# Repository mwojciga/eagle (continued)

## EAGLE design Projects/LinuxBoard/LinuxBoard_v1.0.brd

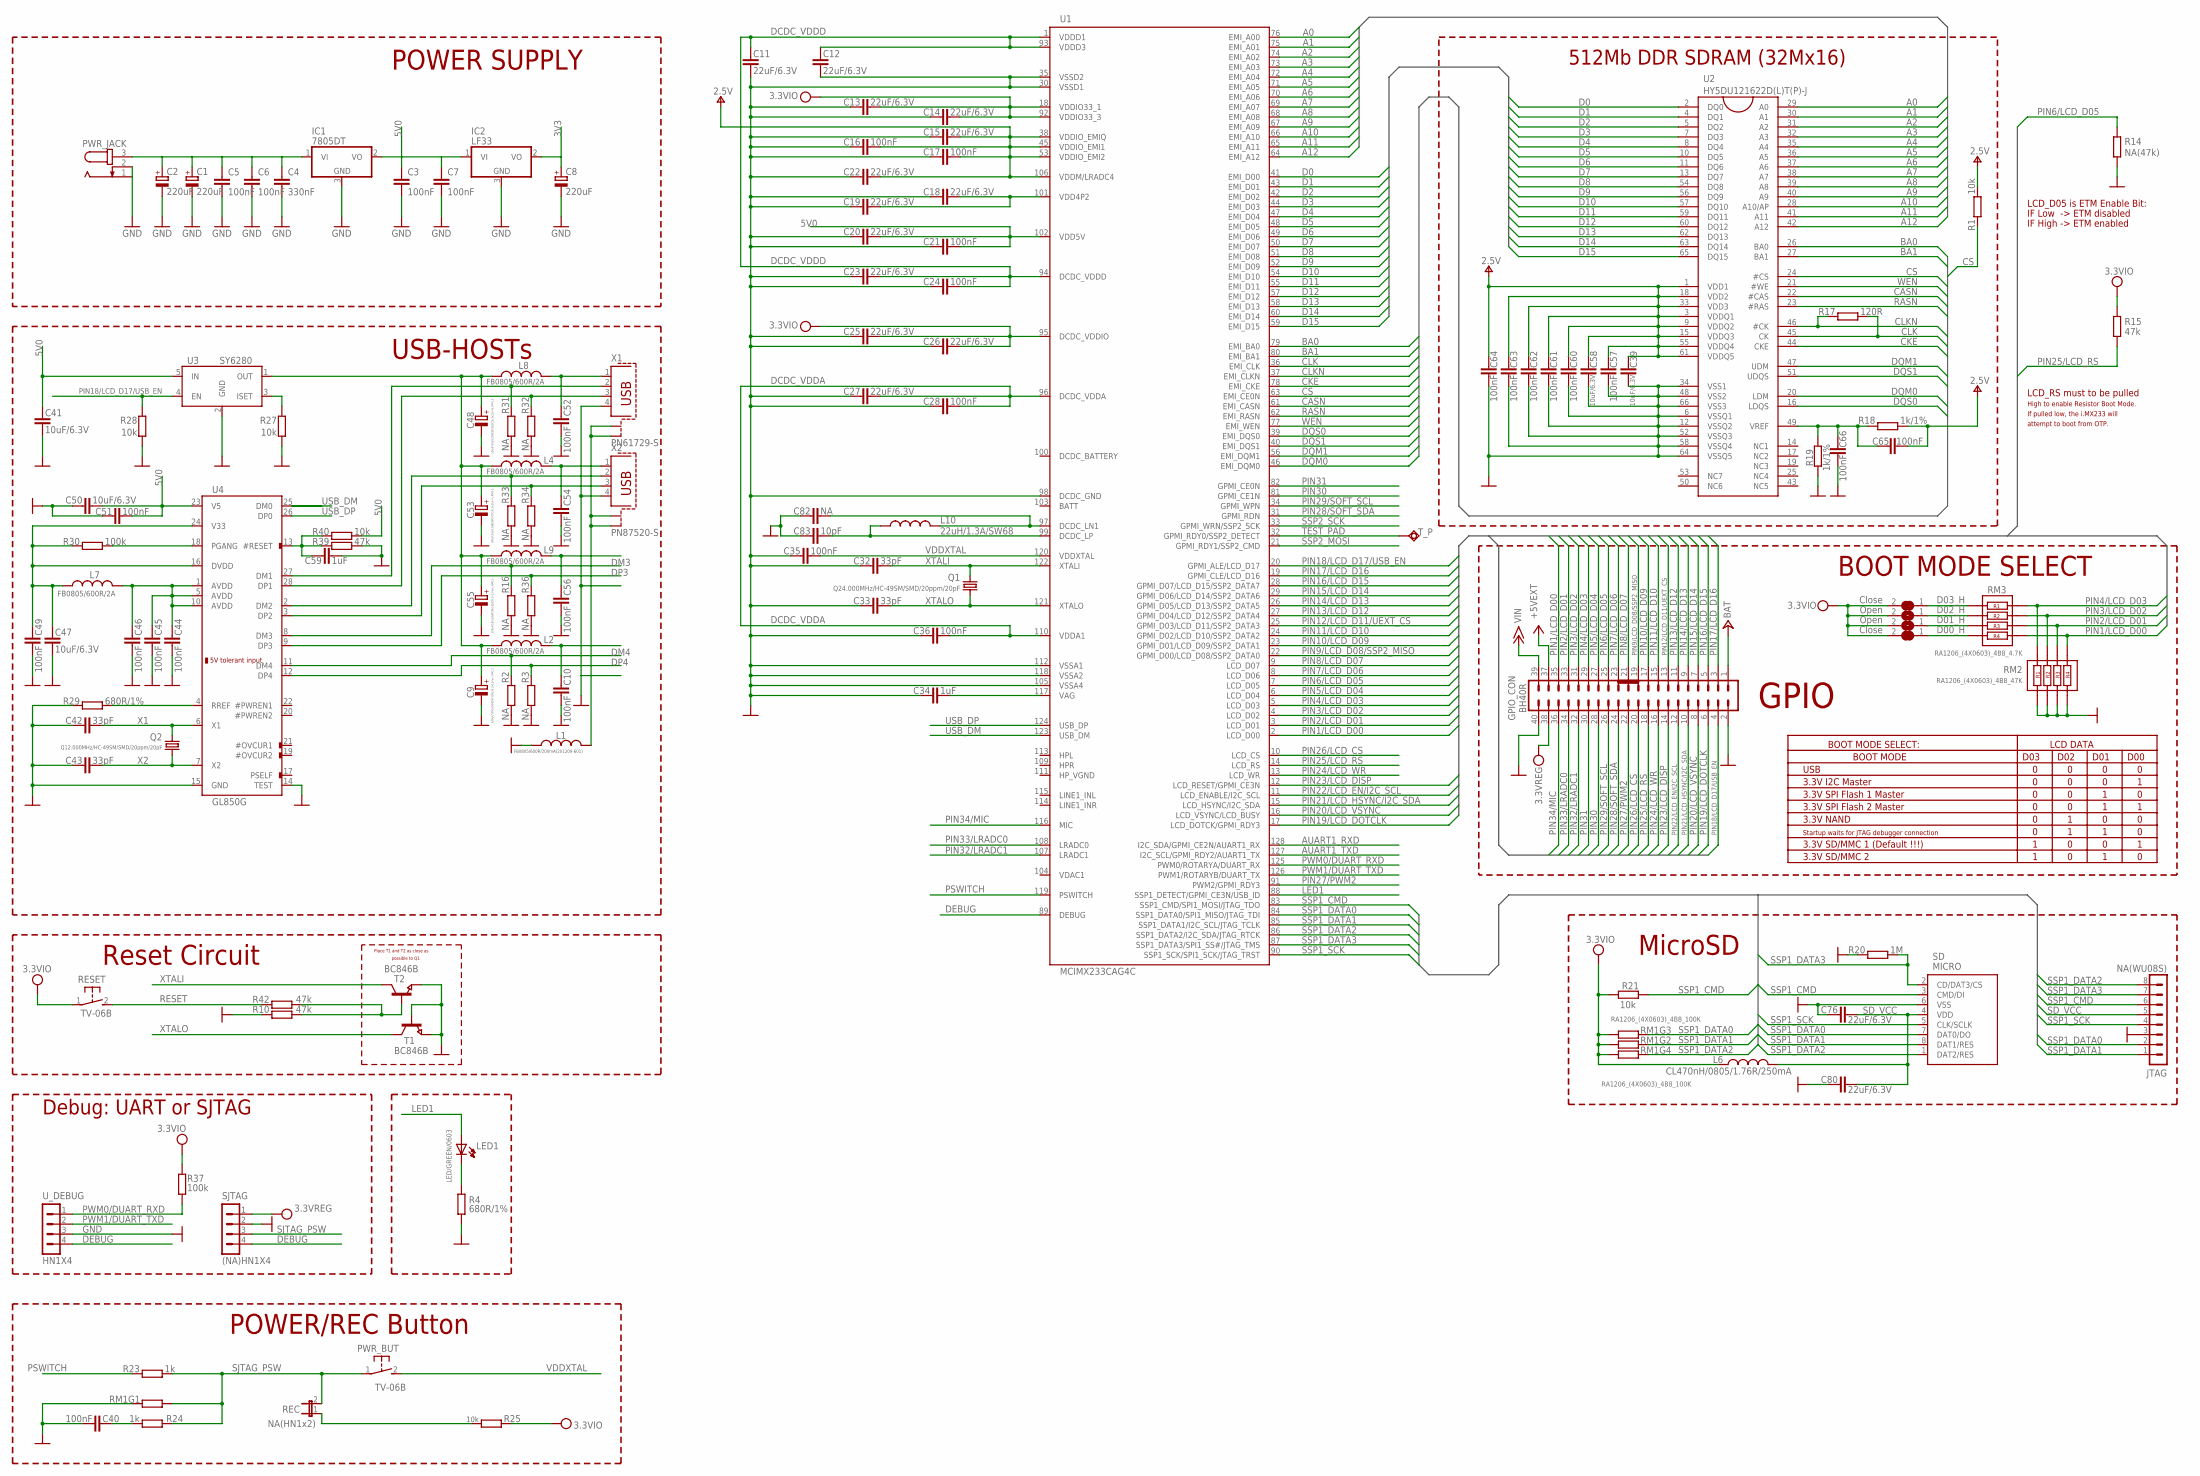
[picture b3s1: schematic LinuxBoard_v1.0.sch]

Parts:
C1, C2, C8: 220uF; E2-5
C3, C5, C6, C7: 100nF; C0805
C4: 330nF; C0805
C9, C48, C53, C55: 100uF/16V/LOWESR/105C/6.3x11mm_RM2.5; E2,5-6,3
C10, C16, C17, C21, C24, C28, C35, C36, C40, C44, C45, C46, C49, C51, C52, C54, C56, C57, C60, C61, C62, C63, C64, C65, C66: 100nF; C0603_DWS
C11, C12, C13, C14, C15, C18, C19, C20, C22, C23, C25, C26, C27, C76, C80: 22uF/6.3V; C0805_5MIL_DWS
C32, C33, C42, C43: 33pF; C0603_DWS
C34, C59: 1uF; C0603_DWS
C39, C41, C47, C50, C58: 10uF/6.3V; C0603_DWS
C82: NA; C0603_DWS
C83: 10pF; C0603_DWS
D00_H, D03_H: Close; SJ_1_SMALLER
D01_H, D02_H: Open; SJ_1_SMALLER
GPIO_CON: BH40R
IC1: 7805DT; TO252
IC2: LF33; TO252
JTAG: NA(WU08S); WU08S
L1: FB0805/600R/200mA(201209-601); L0805_5MIL_DWS
L2, L4, L7, L8, L9: FB0805/600R/2A; L0805_5MIL_DWS
L6: CL470nH/0805/1.76R/250mA; L0805_5MIL_DWS
L10: 22uH/1.3A/SW68; CD53
LED1: LED/GREEN/0603; LED-0603
PWR_BUT: TV-06B; B3F-31XX
PWR_JACK: JACK-PLUG0; SPC4077
Q1: Q24.000MHz/HC-49SM/SMD/20ppm/20pF; HC49/SMD2_THIN
Q2: Q12.000MHz/HC-49SM/SMD/20ppm/20pF; HC49/SMD2_THIN
R1, R21, R27, R28, R40: 10k; R0603_5MIL_DWS
R2, R3, R16, R31, R32, R33, R34, R36: NA; R0603_5MIL_DWS
R4, R29: 680R/1%; R0603_5MIL_DWS
R10, R15, R39, R42: 47k; R0603_5MIL_DWS
R14: NA(47k); R0603_5MIL_DWS
R17: 120R; R0603_5MIL_DWS
R18, R19: 1k/1%; R0603_5MIL_DWS
R20: 1M; R0603_5MIL_DWS
R23, R24: 1k; R0603_5MIL_DWS
R25: 10k; R0603_5MIL_DWS_NA
R30, R37: 100k; R0603_5MIL_DWS
REC: NA(HN1x2); JP1
RESET: TV-06B; B3F-31XX
RM1: RA1206_(4X0603)_4B8_100K; R_MATRIX_4
RM2: RA1206_(4X0603)_4B8_47K; R_MATRIX_4
RM3: RA1206_(4X0603)_4B8_4.7K; R_MATRIX_4
SD: MICRO; TFR-MEM-CON
SJTAG: (NA)HN1X4; HN1X4
T1, T2: BC846B; SOT23
T_P: TESTPAD50/40; SMD50/40
U1: MCIMX233CAG4C; TQFP128LD
U2: HY5DU121622D(L)T(P)-J; 66TSOP-II
U3: SY6280; SOT23-5
U4: GL850G; SSOP28
U_DEBUG: HN1X4
X1: PN61729-S
X2: PN87520-S

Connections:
3V3: C8.+, IC2.2 (VO)
5V0: C3.1, C7.1, C20.2, C21.2, C41.1, C50.1, C51.1, IC1.2 (VO), IC2.1 (VI), R40.2, U1.102 (VDD5V), U3.5 (IN), U4.23 (V5)
+5V: GPIO_CON.37
+15V: GPIO_CON.39
+24V: GPIO_CON.1
A0: U1.76 (EMI_A00), U2.29 (A0)
A1: U1.75 (EMI_A01), U2.30 (A1)
A2: U1.74 (EMI_A02), U2.31 (A2)
A3: U1.73 (EMI_A03), U2.32 (A3)
A4: U1.72 (EMI_A04), U2.35 (A4)
A5: U1.71 (EMI_A05), U2.36 (A5)
A6: U1.70 (EMI_A06), U2.37 (A6)
A7: U1.69 (EMI_A07), U2.38 (A7)
A8: U1.68 (EMI_A08), U2.39 (A8)
A9: U1.67 (EMI_A09), U2.40 (A9)
A10: U1.66 (EMI_A10), U2.28 (A10/AP)
A11: U1.65 (EMI_A11), U2.41 (A11)
A12: U1.64 (EMI_A12), U2.42 (A12)
AUART1_RXD: U1.128 (I2C_SDA/GPMI_CE2N/AUART1_RX)
AUART1_TXD: U1.127 (I2C_SCL/GPMI_RDY2/AUART1_TX)
BA0: U1.79 (EMI_BA0), U2.26 (BA0)
BA1: U1.80 (EMI_BA1), U2.27 (BA1)
CASN: U1.61 (EMI_CASN), U2.22 (#CAS)
CKE: U1.78 (EMI_CKE), U2.44 (CKE)
CLK: R17.2, U1.36 (EMI_CLK), U2.45 (CK)
CLKN: R17.1, U1.37 (EMI_CLKN), U2.46 (#CK)
CS: R1.1, U1.63 (EMI_CE0N), U2.24 (#CS)
D0: U1.41 (EMI_D00), U2.2 (DQ0)
D1: U1.43 (EMI_D01), U2.4 (DQ1)
D2: U1.42 (EMI_D02), U2.5 (DQ2)
D3: U1.44 (EMI_D03), U2.7 (DQ3)
D4: U1.47 (EMI_D04), U2.8 (DQ4)
D5: U1.48 (EMI_D05), U2.10 (DQ5)
D6: U1.49 (EMI_D06), U2.11 (DQ6)
D7: U1.50 (EMI_D07), U2.13 (DQ7)
D8: U1.51 (EMI_D08), U2.54 (DQ8)
D9: U1.52 (EMI_D09), U2.56 (DQ9)
D10: U1.54 (EMI_D10), U2.57 (DQ10)
D11: U1.55 (EMI_D11), U2.59 (DQ11)
D12: U1.57 (EMI_D12), U2.60 (DQ12)
D13: U1.58 (EMI_D13), U2.62 (DQ13)
D14: U1.60 (EMI_D14), U2.63 (DQ14)
D15: U1.59 (EMI_D15), U2.65 (DQ15)
DCDC_BATTERY: U1.100 (DCDC_BATTERY)
DCDC_VDDA: C27.2, C28.2, C36.2, U1.96 (DCDC_VDDA), U1.110 (VDDA1)
DCDC_VDDD: C11.2, C12.2, C23.2, C24.2, U1.1 (VDDD1), U1.93 (VDDD3), U1.94 (DCDC_VDDD)
DEBUG: SJTAG.4, U1.89 (DEBUG), U_DEBUG.4
DM3: R16.2, U4.8 (DM3)
DM4: R2.2, U4.11 (DM4)
DP3: R36.2, U4.9 (DP3)
DP4: R3.2, U4.12 (DP4)
DQM0: U1.46 (EMI_DQM0), U2.20 (LDM)
DQM1: U1.56 (EMI_DQM1), U2.47 (UDM)
DQS0: U1.39 (EMI_DQS0), U2.16 (LDQS)
DQS1: U1.40 (EMI_DQS1), U2.51 (UDQS)
GND: C1.-, C2.-, C3.2, C4.2, C5.2, C6.2, C7.2, C8.-, C9.-, C10.2, C11.1, C12.1, C13.1, C14.1, C15.1, C16.1, C17.1, C18.1, C19.1, C20.1, C21.1, C22.1, C23.1, C24.1, C25.1, C26.1, C27.1, C28.1, C32.1, C33.1, C34.1, C35.1, C36.1, C39.1, C40.2, C41.2, C42.1, C43.1, C44.2, C45.2, C46.2, C47.2, C48.-, C49.2, C50.2, C51.2, C52.2, C53.-, C54.2, C55.-, C56.2, C57.1, C58.1, C59.1, C60.1, C61.1, C62.1, C63.1, C64.1, C66.1, C76.1, C80.1, C82.1, C83.1, GPIO_CON.2, GPIO_CON.40, IC1.3 (GND), IC2.3 (GND), JTAG.3, L1.1, PWR_JACK.1, PWR_JACK.2, R2.1, R3.1, R4.1, R10.2, R14.1, R16.1, R19.1, R20.2, R27.1, R28.1, R29.1, R31.1, R32.1, R33.1, R34.1, R36.1, R39.2, RM1.1.1 (1), RM2.1.1, RM2.2.1, RM2.3.1, RM2.4.1, SD.6 (VSS), SJTAG.2, T1.1 (B), T1.2 (E), T2.2 (E), U1.30 (VSSD1), U1.35 (VSSD2), U1.98 (DCDC_GND), U1.105 (VSSA4), U1.112 (VSSA1), U1.118 (VSSA2), U2.6 (VSSQ1), U2.12 (VSSQ2), U2.34 (VSS1), U2.48 (VSS2), U2.52 (VSSQ3), U2.58 (VSSQ4), U2.64 (VSSQ5), U2.66 (VSS3), U3.2 (GND), U4.14 (TEST), U4.15 (GND), U_DEBUG.3, X1.4, X2.4
HP_VGND: U1.111 (HP_VGND)
LED1: LED1.A, U1.88 (SSP1_DETECT/GPMI_CE3N/USB_ID)
unnamed: R27.2, U3.3 (ISET)
unnamed: R29.2, U4.4 (RREF)
unnamed: R30.2, U4.18 (PGANG)
unnamed: C59.2, R39.1, R40.1, U4.13 (#RESET)
unnamed: C10.1, L2.2
unnamed: C9.+, C48.+, C53.+, C55.+, L2.1, L4.1, L8.1, L9.1, U3.1 (OUT)
unnamed: R31.2, U4.27 (DM1), X1.2
unnamed: C44.1, C45.1, C46.1, L7.2, U4.1 (AVDD), U4.5 (AVDD), U4.10 (AVDD)
unnamed: C47.1, C49.1, L7.1, R30.1, U4.16 (DVDD), U4.24 (V33)
unnamed: R32.2, U4.28 (DP1), X1.3
unnamed: R33.2, U4.2 (DM2), X2.2
unnamed: R34.2, U4.3 (DP2), X2.3
unnamed: L1.2, X1.S1, X1.S2, X2.S1, X2.S2
unnamed: C65.2, C66.2, R18.1, R19.2, U2.49 (VREF)
unnamed: C82.2, L10.2, U1.97 (DCDC_LN1)
unnamed: C83.2, L10.1, U1.99 (DCDC_LP)
unnamed: C52.1, L8.2, X1.1
unnamed: C54.1, L4.2, X2.1
unnamed: C34.2, U1.117 (VAG)
unnamed: C56.1, L9.2
unnamed: C40.1, R24.1
unnamed: R25.1, REC.1
unnamed: LED1.C, R4.2
unnamed: R10.1, R42.1, T2.1 (B)
unnamed: D03_H.1, RM3.1.2
unnamed: D02_H.1, RM3.2.2
unnamed: D01_H.1, RM3.3.2
unnamed: D00_H.1, RM3.4.2
PIN1/LCD_D00: GPIO_CON.35, RM2.4.2, RM3.4.1, U1.2 (LCD_D00)
PIN2/LCD_D01: GPIO_CON.33, RM2.3.2, RM3.3.1, U1.3 (LCD_D01)
PIN3/LCD_D02: GPIO_CON.31, RM2.2.2, RM3.2.1, U1.4 (LCD_D02)
PIN4/LCD_D03: GPIO_CON.29, RM2.1.2, RM3.1.1, U1.5 (LCD_D03)
PIN5/LCD_D04: GPIO_CON.27, U1.6 (LCD_D04)
PIN6/LCD_D05: GPIO_CON.25, R14.2, U1.7 (LCD_D05)
PIN7/LCD_D06: GPIO_CON.23, U1.8 (LCD_D06)
PIN8/LCD_D07: GPIO_CON.21, U1.9 (LCD_D07)
PIN9/LCD_D08/SSP2_MISO: GPIO_CON.19, U1.22 (GPMI_D00/LCD_D08/SSP2_DATA0)
PIN10/LCD_D09: GPIO_CON.17, U1.23 (GPMI_D01/LCD_D09/SSP2_DATA1)
PIN11/LCD_D10: GPIO_CON.15, U1.24 (GPMI_D02/LCD_D10/SSP2_DATA2)
PIN12/LCD_D11/UEXT_CS: GPIO_CON.13, U1.25 (GPMI_D03/LCD_D11/SSP2_DATA3)
PIN13/LCD_D12: GPIO_CON.11, U1.27 (GPMI_D04/LCD_D12/SSP2_DATA4)
PIN14/LCD_D13: GPIO_CON.9, U1.26 (GPMI_D05/LCD_D13/SSP2_DATA5)
PIN15/LCD_D14: GPIO_CON.7, U1.29 (GPMI_D06/LCD_D14/SSP2_DATA6)
PIN16/LCD_D15: GPIO_CON.5, U1.28 (GPMI_D07/LCD_D15/SSP2_DATA7)
PIN17/LCD_D16: GPIO_CON.3, U1.19 (GPMI_CLE/LCD_D16)
PIN18/LCD_D17/USB_EN: GPIO_CON.4, R28.2, U1.20 (GPMI_ALE/LCD_D17), U3.4 (EN)
PIN19/LCD_DOTCLK: GPIO_CON.6, U1.17 (LCD_DOTCK/GPMI_RDY3)
PIN20/LCD_VSYNC: GPIO_CON.8, U1.16 (LCD_VSYNC/LCD_BUSY)
PIN21/LCD_HSYNC/I2C_SDA: GPIO_CON.10, U1.15 (LCD_HSYNC/I2C_SDA)
PIN22/LCD_EN/I2C_SCL: GPIO_CON.12, U1.11 (LCD_ENABLE/I2C_SCL)
PIN23/LCD_DISP: GPIO_CON.14, U1.12 (LCD_RESET/GPMI_CE3N)
PIN24/LCD_WR: GPIO_CON.16, U1.13 (LCD_WR)
PIN25/LCD_RS: GPIO_CON.18, R15.2, U1.14 (LCD_RS)
PIN26/LCD_CS: GPIO_CON.20, U1.10 (LCD_CS)
PIN27/PWM2: GPIO_CON.22, U1.91 (PWM2/GPMI_RDY3)
PIN28/SOFT_SDA: GPIO_CON.24, U1.31 (GPMI_RDN)
PIN29/SOFT_SCL: GPIO_CON.26, U1.34 (GPMI_WPN)
PIN30: GPIO_CON.28, U1.81 (GPMI_CE1N)
PIN31: GPIO_CON.30, U1.82 (GPMI_CE0N)
PIN32/LRADC1: GPIO_CON.32, U1.107 (LRADC1)
PIN33/LRADC0: GPIO_CON.34, U1.108 (LRADC0)
PIN34/MIC: GPIO_CON.36, U1.116 (MIC)
PSWITCH: R23.1, U1.119 (PSWITCH)
PWM0/DUART_RXD: R37.1, U1.125 (PWM0/ROTARYA/DUART_RX), U_DEBUG.1
PWM1/DUART_TXD: U1.126 (PWM1/ROTARYB/DUART_TX), U_DEBUG.2
RASN: U1.62 (EMI_RASN), U2.23 (#RAS)
RESET: R42.2, RESET.2 (S)
SD_VCC: C76.2, C80.2, JTAG.5, L6.2, SD.4 (VDD)
SJTAG_PSW: PWR_BUT.1, R23.2, R24.2, REC.2, RM1.1.2 (2), SJTAG.3
SSP1_CMD: JTAG.6, R21.1, SD.3 (CMD/DI), U1.83 (SSP1_CMD/SPI1_MOSI/JTAG_TDO)
SSP1_DATA0: JTAG.2, RM1.3.1 (1), SD.7 (DAT0/DO), U1.84 (SSP1_DATA0/SPI1_MISO/JTAG_TDI)
SSP1_DATA1: JTAG.1, RM1.2.1 (1), SD.8 (DAT1/RES), U1.85 (SSP1_DATA1/I2C_SCL/JTAG_TCLK)
SSP1_DATA2: JTAG.8, RM1.4.1 (1), SD.1 (DAT2/RES), U1.86 (SSP1_DATA2/I2C_SDA/JTAG_RTCK)
SSP1_DATA3: JTAG.7, R20.1, SD.2 (CD/DAT3/CS), U1.87 (SSP1_DATA3/SPI1_SS#/JTAG_TMS)
SSP1_SCK: JTAG.4, SD.5 (CLK/SCLK), U1.90 (SSP1_SCK/SPI1_SCK/JTAG_TRST)
SSP2_MOSI: U1.21 (GPMI_RDY1/SSP2_CMD)
SSP2_SCK: U1.33 (GPMI_WRN/SSP2_SCK)
TEST_PAD: T_P.P$1, U1.32 (GPMI_RDY0/SSP2_DETECT)
USB_DM: U1.123 (USB_DM), U4.25 (DM0)
USB_DP: U1.124 (USB_DP), U4.26 (DP0)
V+: C15.2, C16.2, C17.2, C22.2, C39.2, C57.2, C58.2, C60.2, C61.2, C62.2, C63.2, C64.2, C65.1, R1.2, R18.2, U1.38 (VDDIO_EMIQ), U1.45 (VDDIO_EMI1), U1.53 (VDDIO_EMI2), U1.106 (VDDM/LRADC4), U2.1 (VDD1), U2.3 (VDDQ1), U2.9 (VDDQ2), U2.15 (VDDQ3), U2.18 (VDD2), U2.33 (VDD3), U2.55 (VDDQ4), U2.61 (VDDQ5)
VCC: GPIO_CON.38, SJTAG.1
VDD4P2: C18.2, C19.2, U1.101 (VDD4P2)
VDDXTAL: C35.2, PWR_BUT.2 (S), U1.120 (VDDXTAL)
VIN_JACK: C1.+, C2.+, C4.1, C5.1, C6.1, IC1.1 (VI), PWR_JACK.3
VPP: C13.2, C14.2, C25.2, C26.2, D00_H.2, D01_H.2, D02_H.2, D03_H.2, L6.1, R15.1, R21.2, R25.2, R37.2, RESET.1, RM1.2.2 (2), RM1.3.2 (2), RM1.4.2 (2), U1.18 (VDDIO33_1), U1.92 (VDDIO33_3), U1.95 (DCDC_VDDIO)
WEN: U1.77 (EMI_WEN), U2.21 (#WE)
X1: C42.2, Q2.2, U4.6 (X1)
X2: C43.2, Q2.1, U4.7 (X2)
XTALI: C32.2, Q1.2, T2.3 (C), U1.122 (XTALI)
XTALO: C33.2, Q1.1, T1.3 (C), U1.121 (XTALO)

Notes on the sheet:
USB-HOSTs
POWER SUPPLY
Place T1 and T2 as close as
possible to Q1
Reset Circuit
512Mb DDR SDRAM (32Mx16)
MicroSD
POWER/REC Button
BOOT MODE SELECT
BOOT MODE SELECT:
LCD DATA
BOOT MODE
D03
D02
D01
D00
USB
3.3V I2C Master
3.3V SPI Flash 1 Master
3.3V SPI Flash 2 Master
3.3V NAND
Startup waits for JTAG debugger connection
3.3V SD/MMC 1 (Default !!!)
3.3V SD/MMC 2
LCD_RS must to be pulled
High to enable Resistor Boot Mode.
If pulled low, the i.MX233 will
attempt to boot from OTP.
LCD_D05 is ETM Enable Bit:
IF Low -> ETM disabled
IF High -> ETM enabled
GPIO
Debug: UART or SJTAG

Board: 2 copper layers, 132 parts (0 on the bottom side), 140 nets, no tracks yet.

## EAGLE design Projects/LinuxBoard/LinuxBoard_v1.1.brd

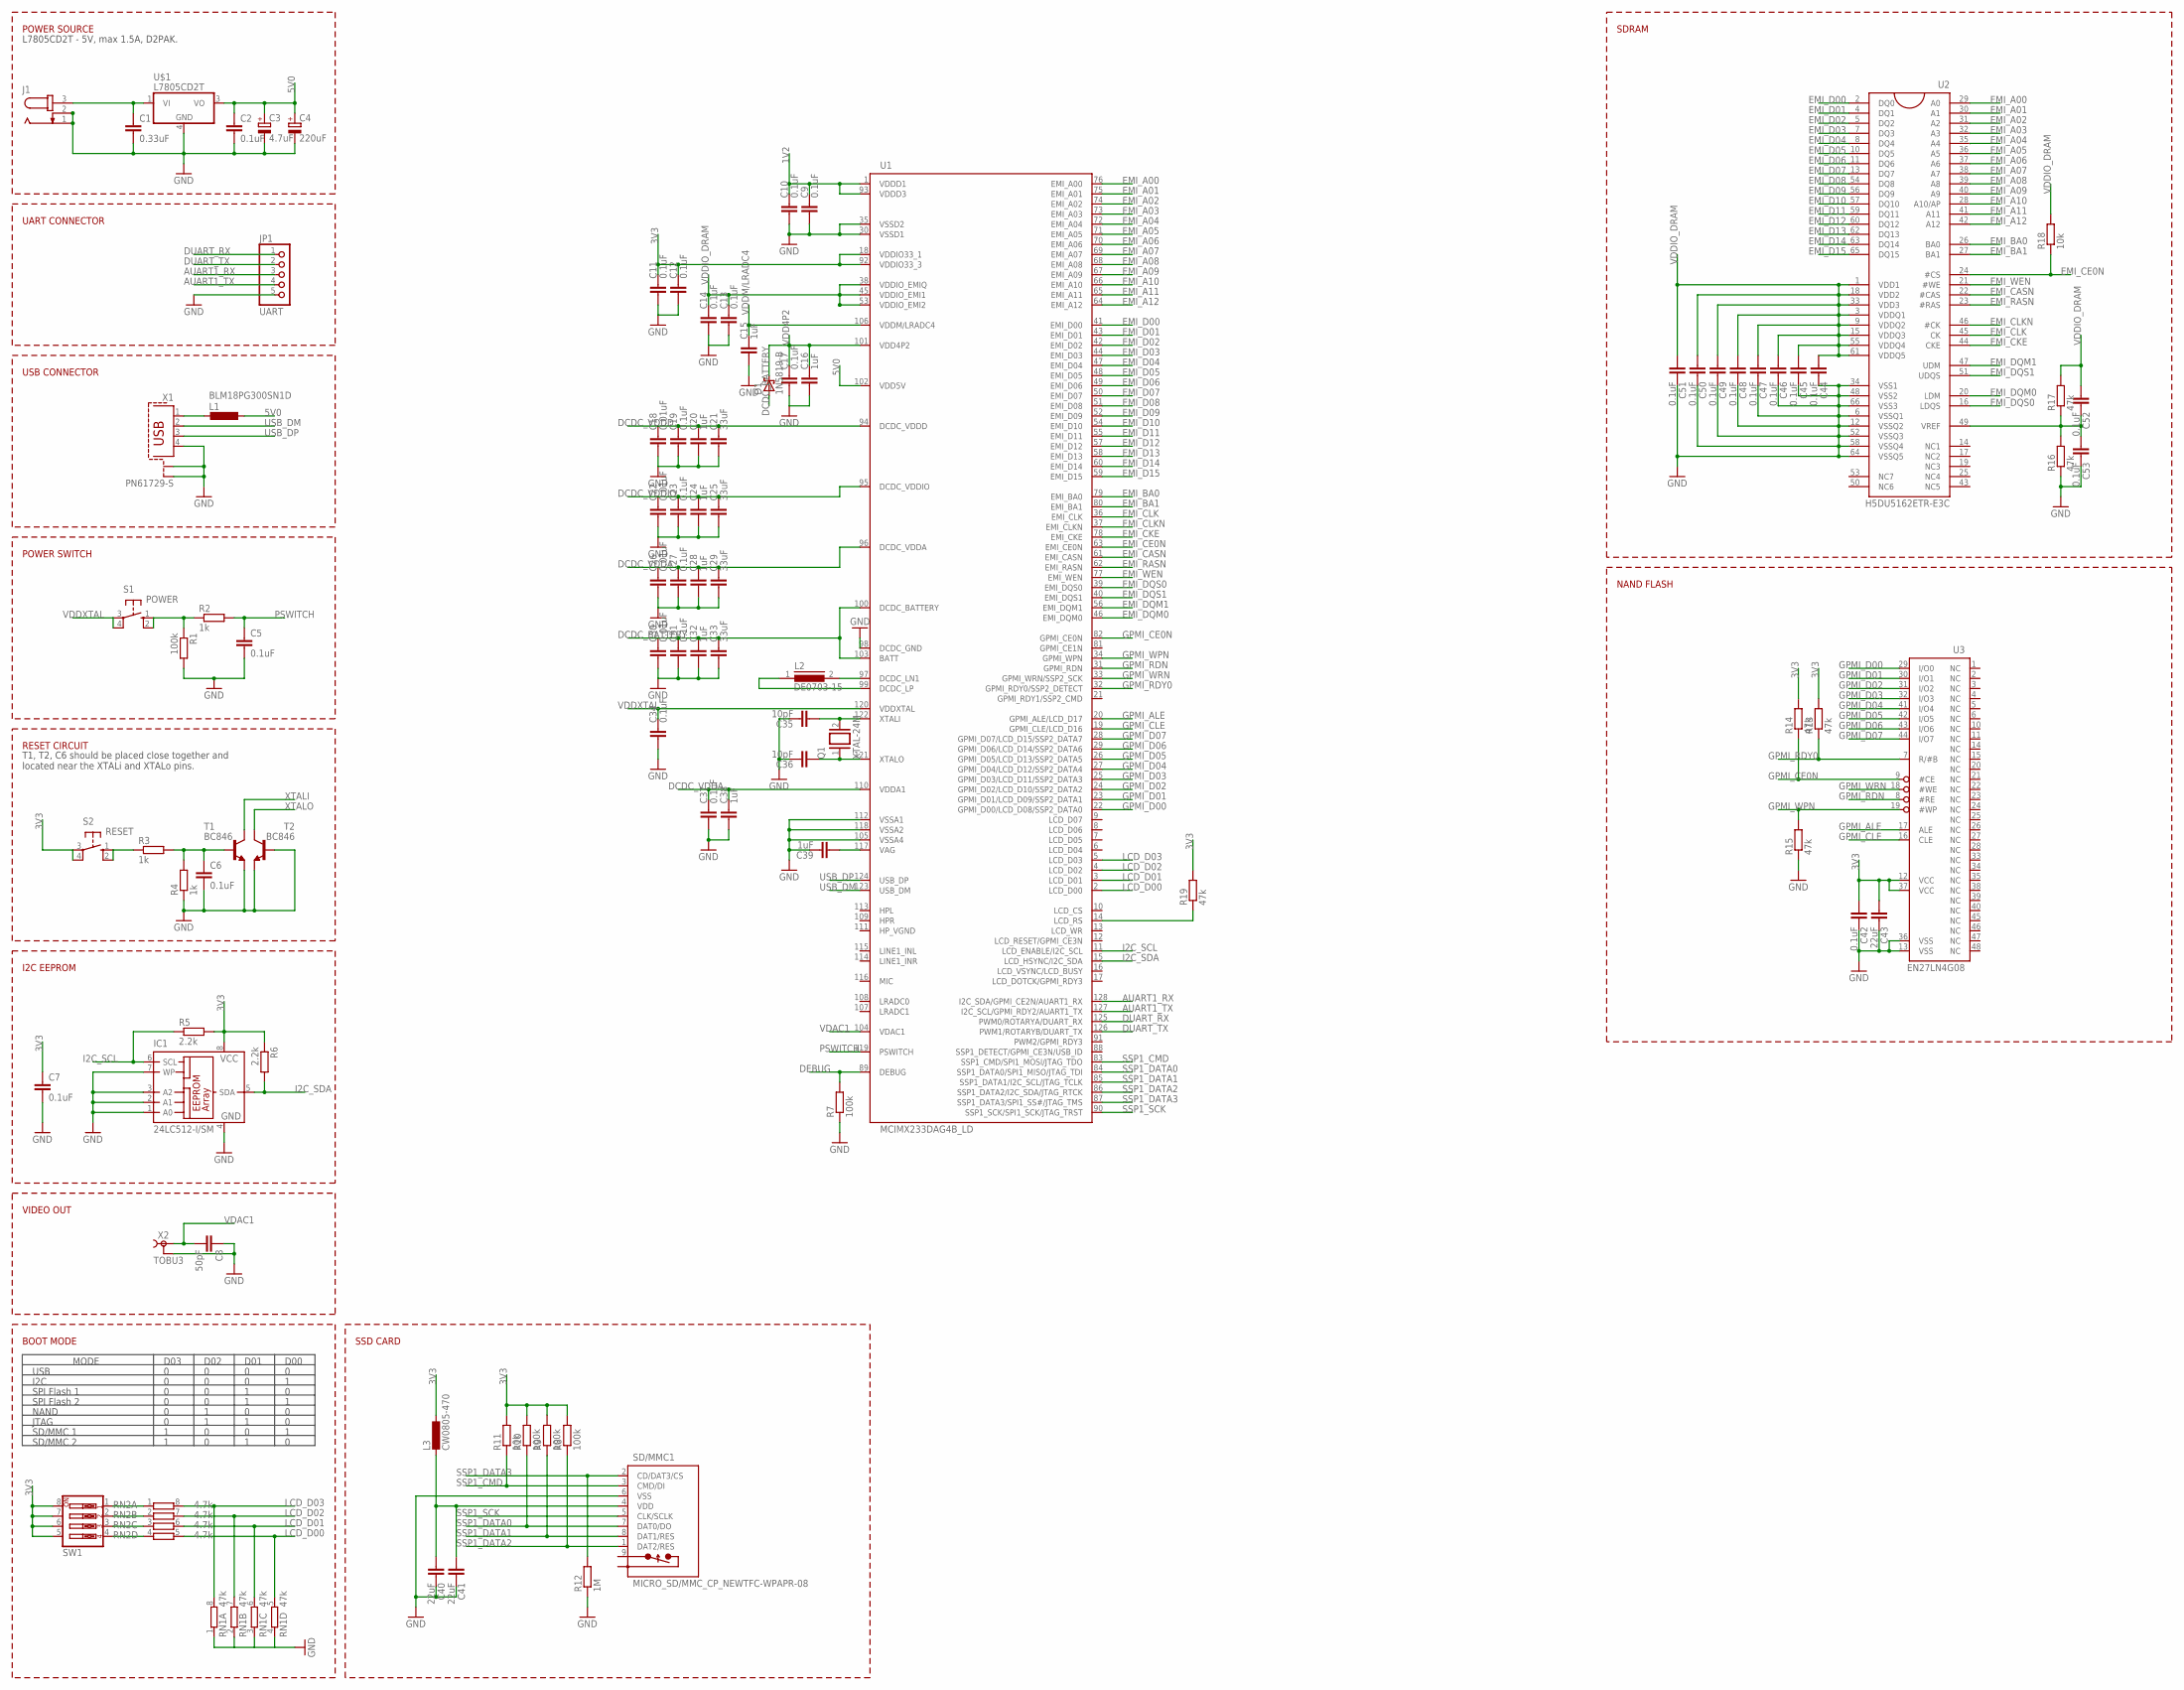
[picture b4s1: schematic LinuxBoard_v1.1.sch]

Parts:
C1: 0.33uF; C0805
C2, C5, C6, C7, C9, C10, C11, C12, C13, C14, C17, C19, C23, C27, C31, C34, C37, C42, C44, C45, C46, C47, C48, C49, C50, C51, C52, C53: 0.1uF; C0805
C3: 4.7uF; E2-5
C4: 220uF; E2-5
C8: 50pF; C0805
C15, C16, C20, C24, C28, C32, C38, C39: 1uF; C0805
C18, C22, C26, C30: 0.01uF; C0805
C21, C25, C29, C33: 33uF; C0805
C35, C36: 10pF; C0805
C40, C41, C43: 22uF; C0805
D1: 1N5819-B; DO41-7.6
IC1: 24LC512-I/SM; SO-08
J1: JACK-PLUG0; SPC4077
JP1: UART; 1X05
L1: BLM18PG300SN1D; L0201
L2: DE0703-15; DR73
L3: CW0805-470; L2012C
Q1: XTAL-24M; QS
R1, R7, R8, R9, R10: 100k; R0805
R2, R3, R4: 1k; R0805
R5, R6: 2.2k; R0805
R11, R18: 10k; R0805
R12: 1M; R0805
R13, R14, R15, R16, R17, R19: 47k; R0805
RN1: 47k; YC124
RN2: 4.7k; YC124
S1: POWER; B3F-10XX
S2: RESET; B3F-10XX
SD/MMC1: MICRO_SD/MMC_CP_NEWTFC-WPAPR-08; TFC-WPAPR-08
SW1: SW_DIP-4; EDG-04
T1, T2: BC846; SOT23
U1: MCIMX233DAG4B_LD; TQFP128LD
U2: H5DU5162ETR-E3C; 66TSOP-II
U3: EN27LN4G08; TSOP48
U$1: L7805CD2T; D2PAK-3
X1: PN61729-S
X2: TOBU3

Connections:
1V2: C9.1, C10.1, U1.1 (VDDD1), U1.93 (VDDD3)
3V3: C7.1, C11.1, C12.1, C42.2, C43.2, IC1.8 (VCC), L3.1, R5.2, R6.1, R8.2, R9.2, R10.2, R11.2, R13.2, R14.2, R19.2, S2.3, S2.4 (P1), SW1.5, SW1.6, SW1.7, SW1.8, U1.18 (VDDIO33_1), U1.92 (VDDIO33_3), U3.12 (VCC), U3.37 (VCC)
5V0: C2.1, C3.+, C4.+, L1.1, U1.102 (VDD5V), U$1.3 (VO)
AUART1_RX: JP1.3, U1.128 (I2C_SDA/GPMI_CE2N/AUART1_RX)
AUART1_TX: JP1.4, U1.127 (I2C_SCL/GPMI_RDY2/AUART1_TX)
DCDC_BATTERY: C30.1, C31.1, C32.1, C33.1, D1.A, U1.100 (DCDC_BATTERY), U1.103 (BATT)
DCDC_VDDA: C26.1, C27.1, C28.1, C29.1, C37.1, C38.1, U1.96 (DCDC_VDDA), U1.110 (VDDA1)
DCDC_VDDD: C18.1, C19.1, C20.1, C21.1, U1.94 (DCDC_VDDD)
DCDC_VDDIO: C22.1, C23.1, C24.1, C25.1, U1.95 (DCDC_VDDIO)
DEBUG: R7.2, U1.89 (DEBUG)
DUART_RX: JP1.1, U1.125 (PWM0/ROTARYA/DUART_RX)
DUART_TX: JP1.2, U1.126 (PWM1/ROTARYB/DUART_TX)
EMI_A00: U1.76 (EMI_A00), U2.29 (A0)
EMI_A01: U1.75 (EMI_A01), U2.30 (A1)
EMI_A02: U1.74 (EMI_A02), U2.31 (A2)
EMI_A03: U1.73 (EMI_A03), U2.32 (A3)
EMI_A04: U1.72 (EMI_A04), U2.35 (A4)
EMI_A05: U1.71 (EMI_A05), U2.36 (A5)
EMI_A06: U1.70 (EMI_A06), U2.37 (A6)
EMI_A07: U1.69 (EMI_A07), U2.38 (A7)
EMI_A08: U1.68 (EMI_A08), U2.39 (A8)
EMI_A09: U1.67 (EMI_A09), U2.40 (A9)
EMI_A10: U1.66 (EMI_A10), U2.28 (A10/AP)
EMI_A11: U1.65 (EMI_A11), U2.41 (A11)
EMI_A12: U1.64 (EMI_A12), U2.42 (A12)
EMI_BA0: U1.79 (EMI_BA0), U2.26 (BA0)
EMI_BA1: U1.80 (EMI_BA1), U2.27 (BA1)
EMI_CASN: U1.61 (EMI_CASN), U2.22 (#CAS)
EMI_CE0N: R18.1, U1.63 (EMI_CE0N), U2.24 (#CS)
EMI_CKE: U1.78 (EMI_CKE), U2.44 (CKE)
EMI_CLK: U1.36 (EMI_CLK), U2.45 (CK)
EMI_CLKN: U1.37 (EMI_CLKN), U2.46 (#CK)
EMI_D00: U1.41 (EMI_D00), U2.2 (DQ0)
EMI_D01: U1.43 (EMI_D01), U2.4 (DQ1)
EMI_D02: U1.42 (EMI_D02), U2.5 (DQ2)
EMI_D03: U1.44 (EMI_D03), U2.7 (DQ3)
EMI_D04: U1.47 (EMI_D04), U2.8 (DQ4)
EMI_D05: U1.48 (EMI_D05), U2.10 (DQ5)
EMI_D06: U1.49 (EMI_D06), U2.11 (DQ6)
EMI_D07: U1.50 (EMI_D07), U2.13 (DQ7)
EMI_D08: U1.51 (EMI_D08), U2.54 (DQ8)
EMI_D09: U1.52 (EMI_D09), U2.56 (DQ9)
EMI_D10: U1.54 (EMI_D10), U2.57 (DQ10)
EMI_D11: U1.55 (EMI_D11), U2.59 (DQ11)
EMI_D12: U1.57 (EMI_D12), U2.60 (DQ12)
EMI_D13: U1.58 (EMI_D13), U2.62 (DQ13)
EMI_D14: U1.60 (EMI_D14), U2.63 (DQ14)
EMI_D15: U1.59 (EMI_D15), U2.65 (DQ15)
EMI_DQM0: U1.46 (EMI_DQM0), U2.20 (LDM)
EMI_DQM1: U1.56 (EMI_DQM1), U2.47 (UDM)
EMI_DQS0: U1.39 (EMI_DQS0), U2.16 (LDQS)
EMI_DQS1: U1.40 (EMI_DQS1), U2.51 (UDQS)
EMI_RASN: U1.62 (EMI_RASN), U2.23 (#RAS)
EMI_WEN: U1.77 (EMI_WEN), U2.21 (#WE)
GND: C1.2, C2.2, C3.-, C4.-, C5.2, C6.2, C7.2, C8.1, C9.2, C10.2, C11.2, C12.2, C13.2, C14.2, C15.2, C16.2, C17.2, C18.2, C19.2, C20.2, C21.2, C22.2, C23.2, C24.2, C25.2, C26.2, C27.2, C28.2, C29.2, C30.2, C31.2, C32.2, C33.2, C34.2, C35.1, C36.1, C37.2, C38.2, C39.1, C40.1, C41.1, C42.1, C43.1, C44.1, C45.1, C46.1, C47.1, C48.1, C49.1, C50.1, C51.1, C53.1, IC1.1 (A0), IC1.2 (A1), IC1.3 (A2), IC1.4 (GND), IC1.7 (WP), J1.1, J1.2, JP1.5, R1.2, R4.1, R7.1, R12.1, R15.1, R16.1, RN1.1, RN1.2 (1), RN1.3 (1), RN1.4 (1), SD/MMC1.6 (VSS), T1.2 (E), T2.1 (B), T2.2 (E), U1.30 (VSSD1), U1.35 (VSSD2), U1.98 (DCDC_GND), U1.105 (VSSA4), U1.112 (VSSA1), U1.118 (VSSA2), U2.6 (VSSQ1), U2.12 (VSSQ2), U2.34 (VSS1), U2.48 (VSS2), U2.52 (VSSQ3), U2.58 (VSSQ4), U2.64 (VSSQ5), U2.66 (VSS3), U3.13 (VSS), U3.36 (VSS), U$1.4 (GND), X1.4, X1.S1, X1.S2, X2.2, X2.2@1 (2), X2.2@2 (2)
GPMI_ALE: U1.20 (GPMI_ALE/LCD_D17), U3.17 (ALE)
GPMI_CE0N: R14.1, U1.82 (GPMI_CE0N), U3.9 (#CE)
GPMI_CLE: U1.19 (GPMI_CLE/LCD_D16), U3.16 (CLE)
GPMI_D00: U1.22 (GPMI_D00/LCD_D08/SSP2_DATA0), U3.29 (I/O0)
GPMI_D01: U1.23 (GPMI_D01/LCD_D09/SSP2_DATA1), U3.30 (I/O1)
GPMI_D02: U1.24 (GPMI_D02/LCD_D10/SSP2_DATA2), U3.31 (I/O2)
GPMI_D03: U1.25 (GPMI_D03/LCD_D11/SSP2_DATA3), U3.32 (I/O3)
GPMI_D04: U1.27 (GPMI_D04/LCD_D12/SSP2_DATA4), U3.41 (I/O4)
GPMI_D05: U1.26 (GPMI_D05/LCD_D13/SSP2_DATA5), U3.42 (I/O5)
GPMI_D06: U1.29 (GPMI_D06/LCD_D14/SSP2_DATA6), U3.43 (I/O6)
GPMI_D07: U1.28 (GPMI_D07/LCD_D15/SSP2_DATA7), U3.44 (I/O7)
GPMI_RDN: U1.31 (GPMI_RDN), U3.8 (#RE)
GPMI_RDY0: R13.1, U1.32 (GPMI_RDY0/SSP2_DETECT), U3.7 (R/#B)
GPMI_WPN: R15.2, U1.34 (GPMI_WPN), U3.19 (#WP)
GPMI_WRN: U1.33 (GPMI_WRN/SSP2_SCK), U3.18 (#WE)
HP_VGND: U1.111 (HP_VGND)
I2C_SCL: IC1.6 (SCL), R5.1, U1.11 (LCD_ENABLE/I2C_SCL)
I2C_SDA: IC1.5 (SDA), R6.2, U1.15 (LCD_HSYNC/I2C_SDA)
LCD_D00: RN1.5 (2), RN2.5 (2), U1.2 (LCD_D00)
LCD_D01: RN1.6 (2), RN2.6 (2), U1.3 (LCD_D01)
LCD_D02: RN1.7 (2), RN2.7 (2), U1.4 (LCD_D02)
LCD_D03: RN1.8 (2), RN2.8 (2), U1.5 (LCD_D03)
unnamed: C1.1, J1.3, U$1.1 (VI)
unnamed: R3.1, S2.1 (S), S2.2 (S1)
unnamed: R1.1, R2.1, S1.1 (S), S1.2 (S1)
unnamed: C6.1, R3.2, R4.2, T1.1 (B)
unnamed: RN2.1, SW1.1
unnamed: RN2.2 (1), SW1.2
unnamed: RN2.3 (1), SW1.3
unnamed: RN2.4 (1), SW1.4
unnamed: L2.2, U1.97 (DCDC_LN1)
unnamed: L1.2, X1.1
unnamed: L2.1, U1.99 (DCDC_LP)
unnamed: C39.2, U1.117 (VAG)
unnamed: R19.1, U1.14 (LCD_RS)
unnamed: C40.2, C41.2, L3.2, SD/MMC1.4 (VDD)
unnamed: C52.1, C53.2, R16.2, R17.1, U2.49 (VREF)
PSWITCH: C5.1, R2.2, U1.119 (PSWITCH)
SSP1_CMD: R11.1, SD/MMC1.3 (CMD/DI), U1.83 (SSP1_CMD/SPI1_MOSI/JTAG_TDO)
SSP1_DATA0: R10.1, SD/MMC1.7 (DAT0/DO), U1.84 (SSP1_DATA0/SPI1_MISO/JTAG_TDI)
SSP1_DATA1: R9.1, SD/MMC1.8 (DAT1/RES), U1.85 (SSP1_DATA1/I2C_SCL/JTAG_TCLK)
SSP1_DATA2: R8.1, SD/MMC1.1 (DAT2/RES), U1.86 (SSP1_DATA2/I2C_SDA/JTAG_RTCK)
SSP1_DATA3: R12.2, SD/MMC1.2 (CD/DAT3/CS), U1.87 (SSP1_DATA3/SPI1_SS#/JTAG_TMS)
SSP1_SCK: SD/MMC1.5 (CLK/SCLK), U1.90 (SSP1_SCK/SPI1_SCK/JTAG_TRST)
USB_DM: U1.123 (USB_DM), X1.2
USB_DP: U1.124 (USB_DP), X1.3
VDAC1: C8.2, U1.104 (VDAC1), X2.1
VDD4P2: C16.1, C17.1, D1.C, U1.101 (VDD4P2)
VDDIO_DRAM: C13.1, C14.1, C44.2, C45.2, C46.2, C47.2, C48.2, C49.2, C50.2, C51.2, C52.2, R17.2, R18.2, U1.38 (VDDIO_EMIQ), U1.45 (VDDIO_EMI1), U1.53 (VDDIO_EMI2), U2.1 (VDD1), U2.3 (VDDQ1), U2.9 (VDDQ2), U2.15 (VDDQ3), U2.18 (VDD2), U2.33 (VDD3), U2.55 (VDDQ4), U2.61 (VDDQ5)
VDDM/LRADC4: C15.1, U1.106 (VDDM/LRADC4)
VDDXTAL: C34.1, S1.3, S1.4 (P1), U1.120 (VDDXTAL)
XTALI: C35.2, Q1.2, T1.3 (C), U1.122 (XTALI)
XTALO: C36.2, Q1.1, T2.3 (C), U1.121 (XTALO)

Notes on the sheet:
L7805CD2T - 5V, max 1.5A, D2PAK.
POWER SOURCE
UART CONNECTOR
USB CONNECTOR
POWER SWITCH
RESET CIRCUIT
T1, T2, C6 should be placed close together and located near the XTALi and XTALo pins.
I2C EEPROM
VIDEO OUT
BOOT MODE
MODE
D03
D02
D01
D00
USB
I2C
SPI Flash 1
SPI Flash 2
NAND
JTAG
SD/MMC 1
SD/MMC 2
SSD CARD
SDRAM
NAND FLASH

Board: 2 copper layers, 94 parts (14 on the bottom side), 107 nets, no tracks yet.
